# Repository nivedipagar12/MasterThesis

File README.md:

# MasterThesis
This repository contains the python code associated with my Master Thesis titled **"Evaluation and Feasibility Study of Analog Sensor Front-End using Impedance Spectroscopy for Biomedical Application"**. If you are new to this field, I suggest reading a little about the following topic:

- **Cole Model** : [Need of cole model and curve fitting for Body Composition Analysis](https://iopscience.iop.org/article/10.1088/0967-3334/34/10/1239)

1) **Folder Name: Curve Fitting**

This folder contains the main curve fitting algorithm. In the above mentioned cole modelling paper, you will find the formulas used to find the initial values of **x0, y0 and r0 (Equation 5)** and the simplified formula used to implement the **BFGS** algorithm to find the result as a function of **F(x0, y0, r0)** **(Equation 3)**. Upon finding the **center** **(x0,y0)** and **radius** **r0** of the imaginary circle, the **R0** and **Rinf** values can be calculated using distance formula as follows :

Point 1: x0,y0
Point 2: R0 or Rinf,0 .. Since the points R0 and Rinf are on x axis, their y-coordinate will be 0
distance = r0 .. We already know the distance between the two points (r0) 

Reverse engineering the distance formula, we can find R0 and Rinf as follows:
- R_{0} = x_{0} + \sqrt{r_{0}^{2} - y_{0}^{2}} .. to find R0
- R_{\infty}  = x_{0} - \sqrt{r_{0}^{2} - y_{0}^{2}} .. to find Rinf

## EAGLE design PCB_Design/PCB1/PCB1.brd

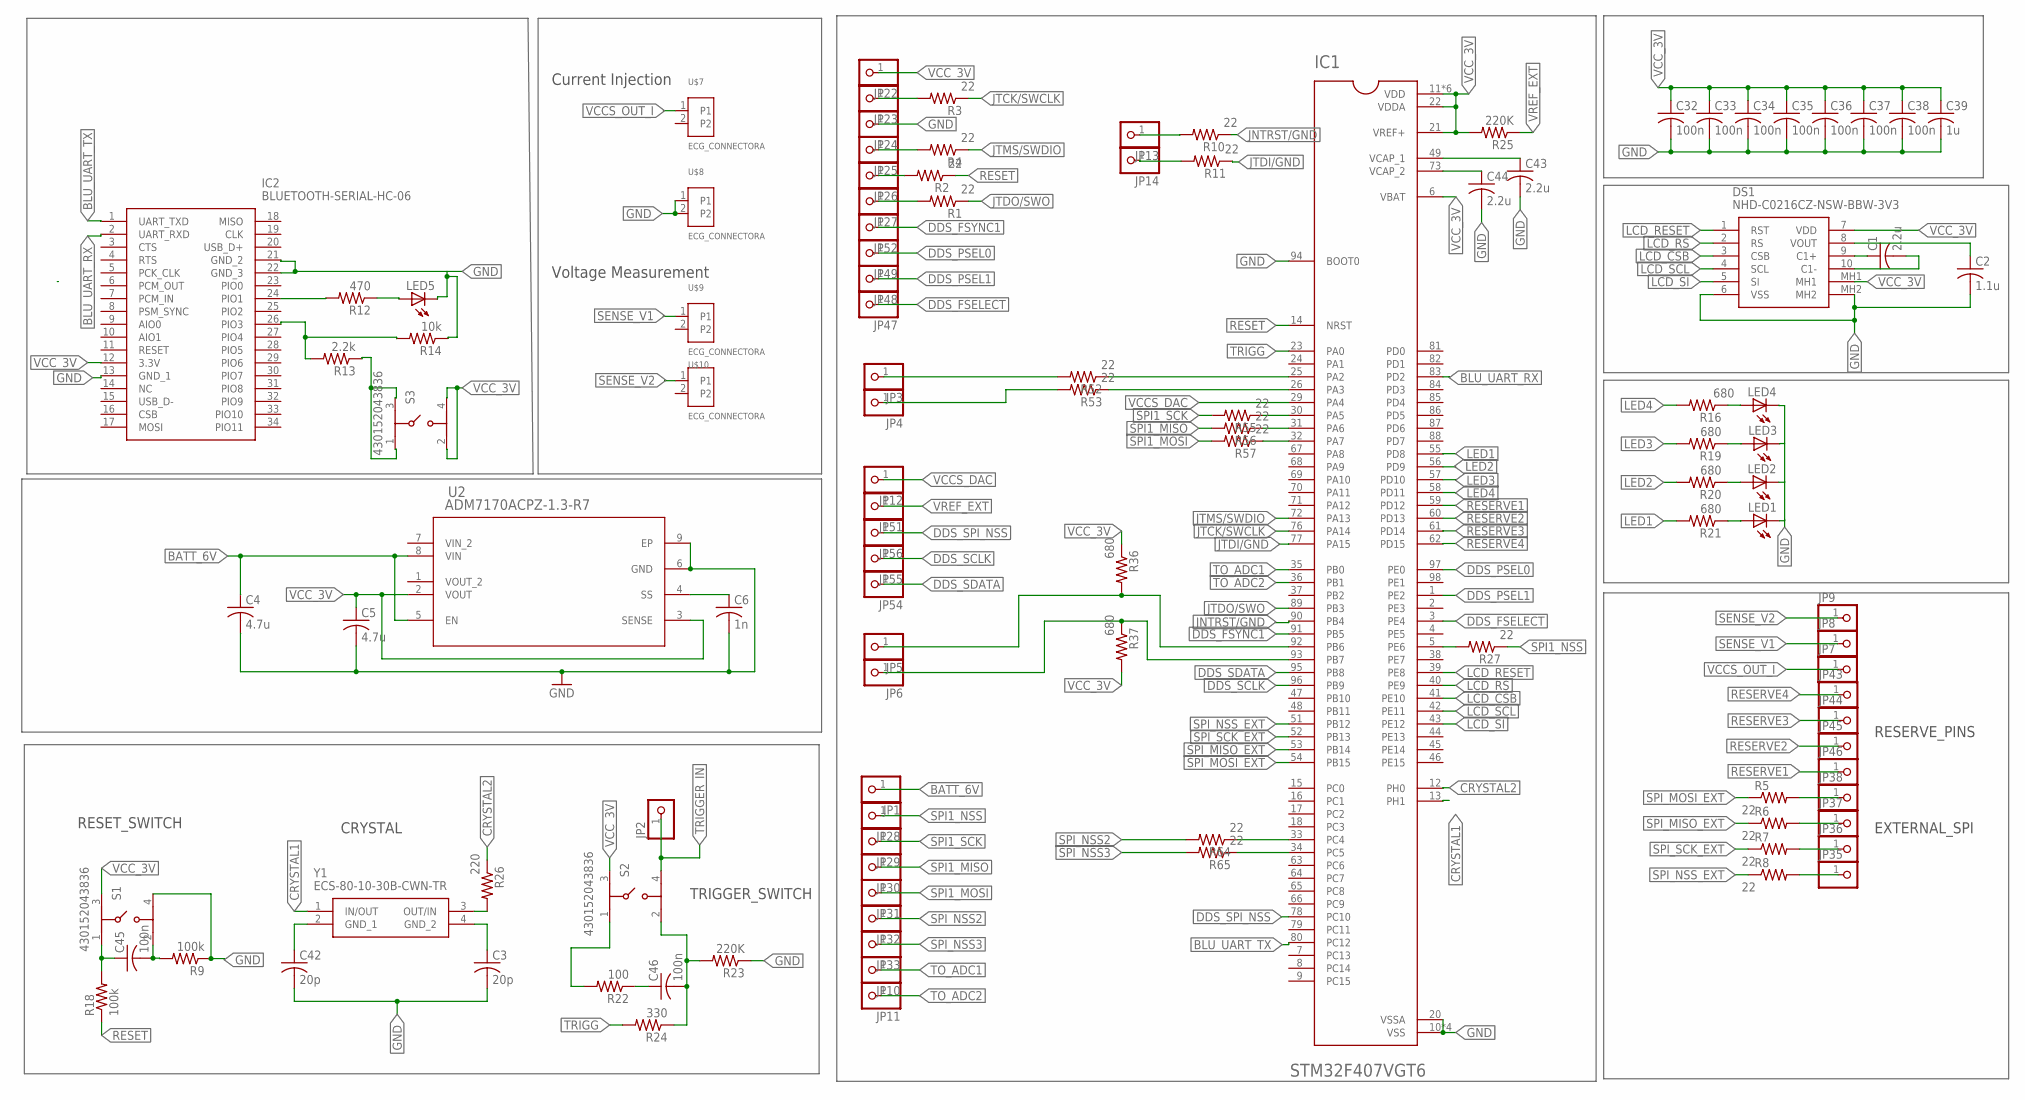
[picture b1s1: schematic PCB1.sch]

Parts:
C1, C43, C44: 2.2u; C0603
C2: 1.1u; C0603
C3, C42: 20p; C0603
C4, C5: 4.7u; C0603
C6: 1n; C0603
C32, C33, C34, C35, C36, C37, C38, C45, C46: 100n; C0603
C39: 1u; C0603
DS1: NHD-C0216CZ-NSW-BBW-3V3; NHDC0216CZNSWBBW3V3
IC1: STM32F407VGT6; QFP50P1600X1600X160-100N
IC2: BLUETOOTH-SERIAL-HC-06; BLUETOOTHSERIALHC06
JP1, JP2, JP3, JP4, JP5, JP6, JP7, JP8, JP9, JP10, JP11, JP12, JP13, JP14, JP22, JP23, JP24, JP25, JP26, JP27, JP28, JP29, JP30, JP31, JP32, JP33, JP35, JP36, JP37, JP38, JP43, JP44, JP45, JP46, JP47, JP48, JP49, JP51, JP52, JP54, JP55, JP56: PINHD-1X1; 1X01
LED1, LED2, LED3, LED4, LED5: LEDCHIPLED_1206; CHIPLED_1206
R1, R2, R3, R4, R5, R6, R7, R8, R10, R11, R27, R52, R53, R55, R56, R57, R64, R65: 22; R0603
R9, R18: 100k; R0603
R12: 470; R0603
R13: 2.2k; R0603
R14: 10k; R0603
R16, R19, R20, R21, R36, R37: 680; R0603
R22: 100; R0603
R23, R25: 220K; R0603
R24: 330; R0603
R26: 220; R0603
S1, S2, S3: 430152043836
U2: ADM7170ACPZ-1.3-R7; CP_8_21
U$7, U$8, U$9, U$10: ECG_CONNECTORA; ECG_CONNECTOR
Y1: ECS-80-10-30B-CWN-TR; ECS801830BAGNTR

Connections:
BATT_6V: C4.1, JP1.1, U2.5 (EN), U2.8 (VIN)
BLU_UART_RX: IC1.83 (PD2), IC2.2 (UART_RXD)
BLU_UART_TX: IC1.80 (PC12), IC2.1 (UART_TXD)
CRYSTAL1: IC1.13 (PH1), Y1.1 (IN/OUT)
CRYSTAL2: IC1.12 (PH0), R26.1
DDS_FSELECT: IC1.3 (PE4), JP47.1
DDS_FSYNC1: IC1.91 (PB5), JP52.1
DDS_PSEL0: IC1.97 (PE0), JP49.1
DDS_PSEL1: IC1.1 (PE2), JP48.1
DDS_SCLK: IC1.96 (PB9), JP55.1
DDS_SDATA: IC1.95 (PB8), JP54.1
DDS_SPI_NSS: IC1.78 (PC10), JP56.1
GND: C2.2, C3.2, C4.2, C5.2, C6.2, C32.2, C33.2, C34.2, C35.2, C36.2, C37.2, C38.2, C39.2, C42.1, C42.2, C43.2, C44.2, DS1.6 (VSS), DS1.MH2, IC1.10 (VSS), IC1.20 (VSSA), IC1.27 (VSS), IC1.74 (VSS), IC1.94 (BOOT0), IC1.99 (VSS), IC2.13 (GND_1), IC2.21 (GND_2), IC2.22 (GND_3), JP24.1, LED1.C, LED2.C, LED3.C, LED4.C, LED5.C, R9.1, R14.1, R23.1, S1.4, U2.6 (GND), U2.9 (EP), U$8.1, U$8.2, Y1.2 (GND_1)
I2C_SCL: IC1.92 (PB6), JP5.1, R36.2
I2C_SDA: IC1.93 (PB7), JP6.1, R37.1
JNTRST/GND: IC1.90 (PB4), R10.1
JTCK/SWCLK: IC1.76 (PA14), R3.1
JTDI/GND: IC1.77 (PA15), R11.1
JTDO/SWO: IC1.89 (PB3), R1.1
JTMS/SWDIO: IC1.72 (PA13), R4.1
LCD_CSB: DS1.3 (CSB), IC1.41 (PE10)
LCD_RESET: DS1.1 (RST), IC1.39 (PE8)
LCD_RS: DS1.2 (RS), IC1.40 (PE9)
LCD_SCL: DS1.4 (SCL), IC1.42 (PE11)
LCD_SI: DS1.5 (SI), IC1.43 (PE12)
LED1: IC1.55 (PD8), R21.2
LED2: IC1.56 (PD9), R20.2
LED3: IC1.57 (PD10), R19.2
LED4: IC1.58 (PD11), R16.2
unnamed: JP27.1, R1.2
unnamed: C1.1, DS1.9 (C1+)
unnamed: C45.2, R9.2, S1.2
unnamed: C1.2, DS1.10 (C1-)
unnamed: JP26.1, R2.2
unnamed: JP25.1, R4.2
unnamed: JP13.1, R10.2
unnamed: JP23.1, R3.2
unnamed: C2.1, DS1.8 (VOUT)
unnamed: JP35.1, R8.2
unnamed: C6.1, U2.4 (SS)
unnamed: JP36.1, R7.2
unnamed: JP37.1, R6.2
unnamed: JP38.1, R5.2
unnamed: JP14.1, R11.2
unnamed: R13.1, S3.1, S3.3
unnamed: LED2.A, R20.1
unnamed: LED3.A, R19.1
unnamed: LED4.A, R16.1
unnamed: LED1.A, R21.1
unnamed: IC2.24 (PIO1), R12.2
unnamed: LED5.A, R12.1
unnamed: R22.2, S2.1
unnamed: IC1.5 (PE6), R27.2
unnamed: C46.1, R22.1
unnamed: C43.1, IC1.49 (VCAP_1)
unnamed: C44.1, IC1.73 (VCAP_2)
unnamed: C46.2, R23.2, R24.1, S2.2
unnamed: C45.1, R18.2, S1.1
unnamed: C3.1, Y1.4 (GND_2)
unnamed: R26.2, Y1.3 (OUT/IN)
unnamed: IC2.26 (PIO3), R13.2, R14.2
unnamed: JP3.1, R52.2
unnamed: JP4.1, R53.2
unnamed: IC1.25 (PA2), R52.1
unnamed: IC1.26 (PA3), R53.1
unnamed: IC1.33 (PC4), R64.1
unnamed: IC1.30 (PA5), R55.1
unnamed: IC1.31 (PA6), R56.1
unnamed: IC1.32 (PA7), R57.1
unnamed: IC1.34 (PC5), R65.1
RESERVE1: IC1.59 (PD12), JP46.1
RESERVE2: IC1.60 (PD13), JP45.1
RESERVE3: IC1.61 (PD14), JP44.1
RESERVE4: IC1.62 (PD15), JP43.1
RESET: IC1.14 (NRST), R2.1, R18.1
SENSE_V1: JP8.1, U$9.1
SENSE_V2: JP9.1, U$10.1
SPI1_MISO: JP30.1, R56.2
SPI1_MOSI: JP31.1, R57.2
SPI1_NSS: JP28.1, R27.1
SPI1_SCK: JP29.1, R55.2
SPI_MISO_EXT: IC1.53 (PB14), R6.1
SPI_MOSI_EXT: IC1.54 (PB15), R5.1
SPI_NSS2: JP32.1, R64.2
SPI_NSS3: JP33.1, R65.2
SPI_NSS_EXT: IC1.51 (PB12), R8.1
SPI_SCK_EXT: IC1.52 (PB13), R7.1
TO_ADC1: IC1.35 (PB0), JP10.1
TO_ADC2: IC1.36 (PB1), JP11.1
TRIGG: IC1.23 (PA0), R24.2
TRIGGER_IN: JP2.1, S2.4
VCCS_DAC: IC1.29 (PA4), JP12.1
VCCS_OUT_I: JP7.1, U$7.1
VCC_3V: C5.1, C32.1, C33.1, C34.1, C35.1, C36.1, C37.1, C38.1, C39.1, DS1.7 (VDD), DS1.MH1, IC1.6 (VBAT), IC1.11 (VDD), IC1.19 (VDD), IC1.21 (VREF+), IC1.22 (VDDA), IC1.28 (VDD), IC1.50 (VDD), IC1.75 (VDD), IC1.100 (VDD), IC2.12 (3.3V), JP22.1, R25.2, R36.1, R37.2, S1.3, S2.3, S3.2, S3.4, U2.2 (VOUT), U2.3 (SENSE)
VREF_EXT: JP51.1, R25.1

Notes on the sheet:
Current Injection
Voltage Measurement
RESET_SWITCH
CRYSTAL
TRIGGER_SWITCH
RESERVE_PINS
EXTERNAL_SPI

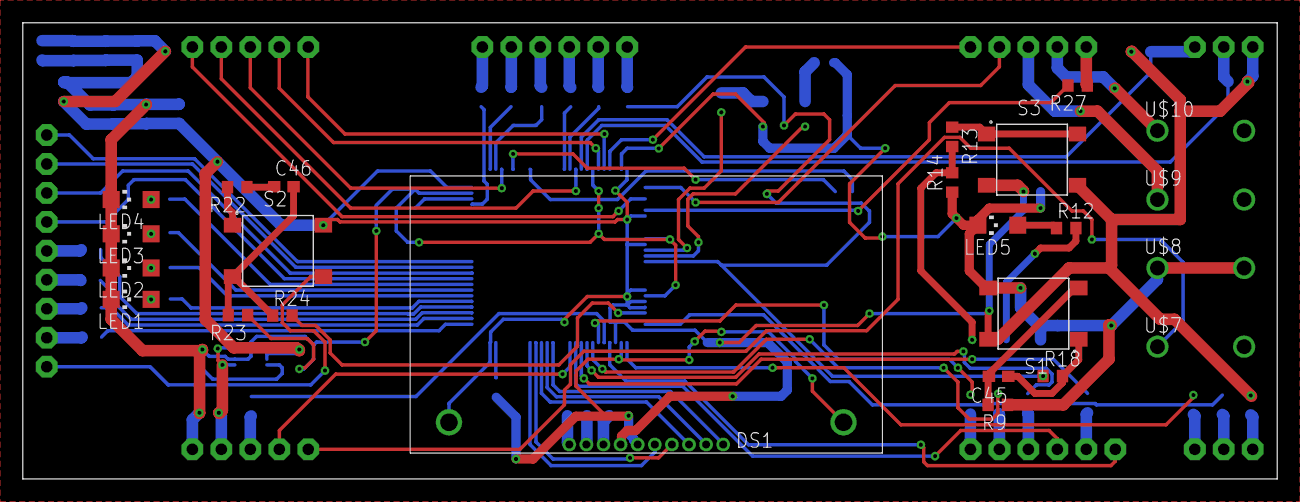
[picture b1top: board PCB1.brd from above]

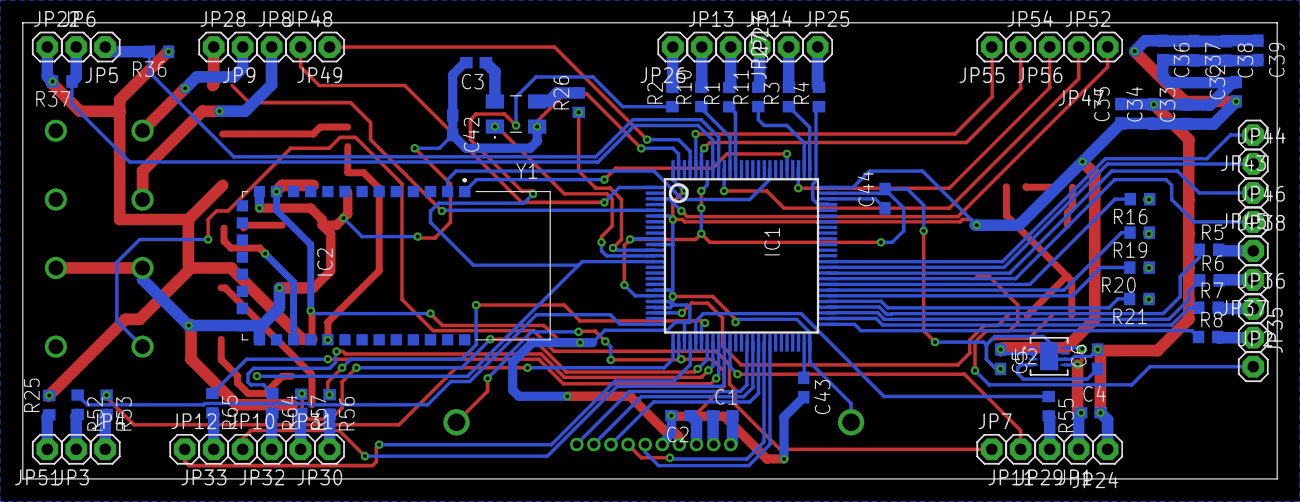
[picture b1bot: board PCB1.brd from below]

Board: 2 copper layers, 110.0 x 40.0 mm, 112 parts (88 on the bottom side), 95 nets.

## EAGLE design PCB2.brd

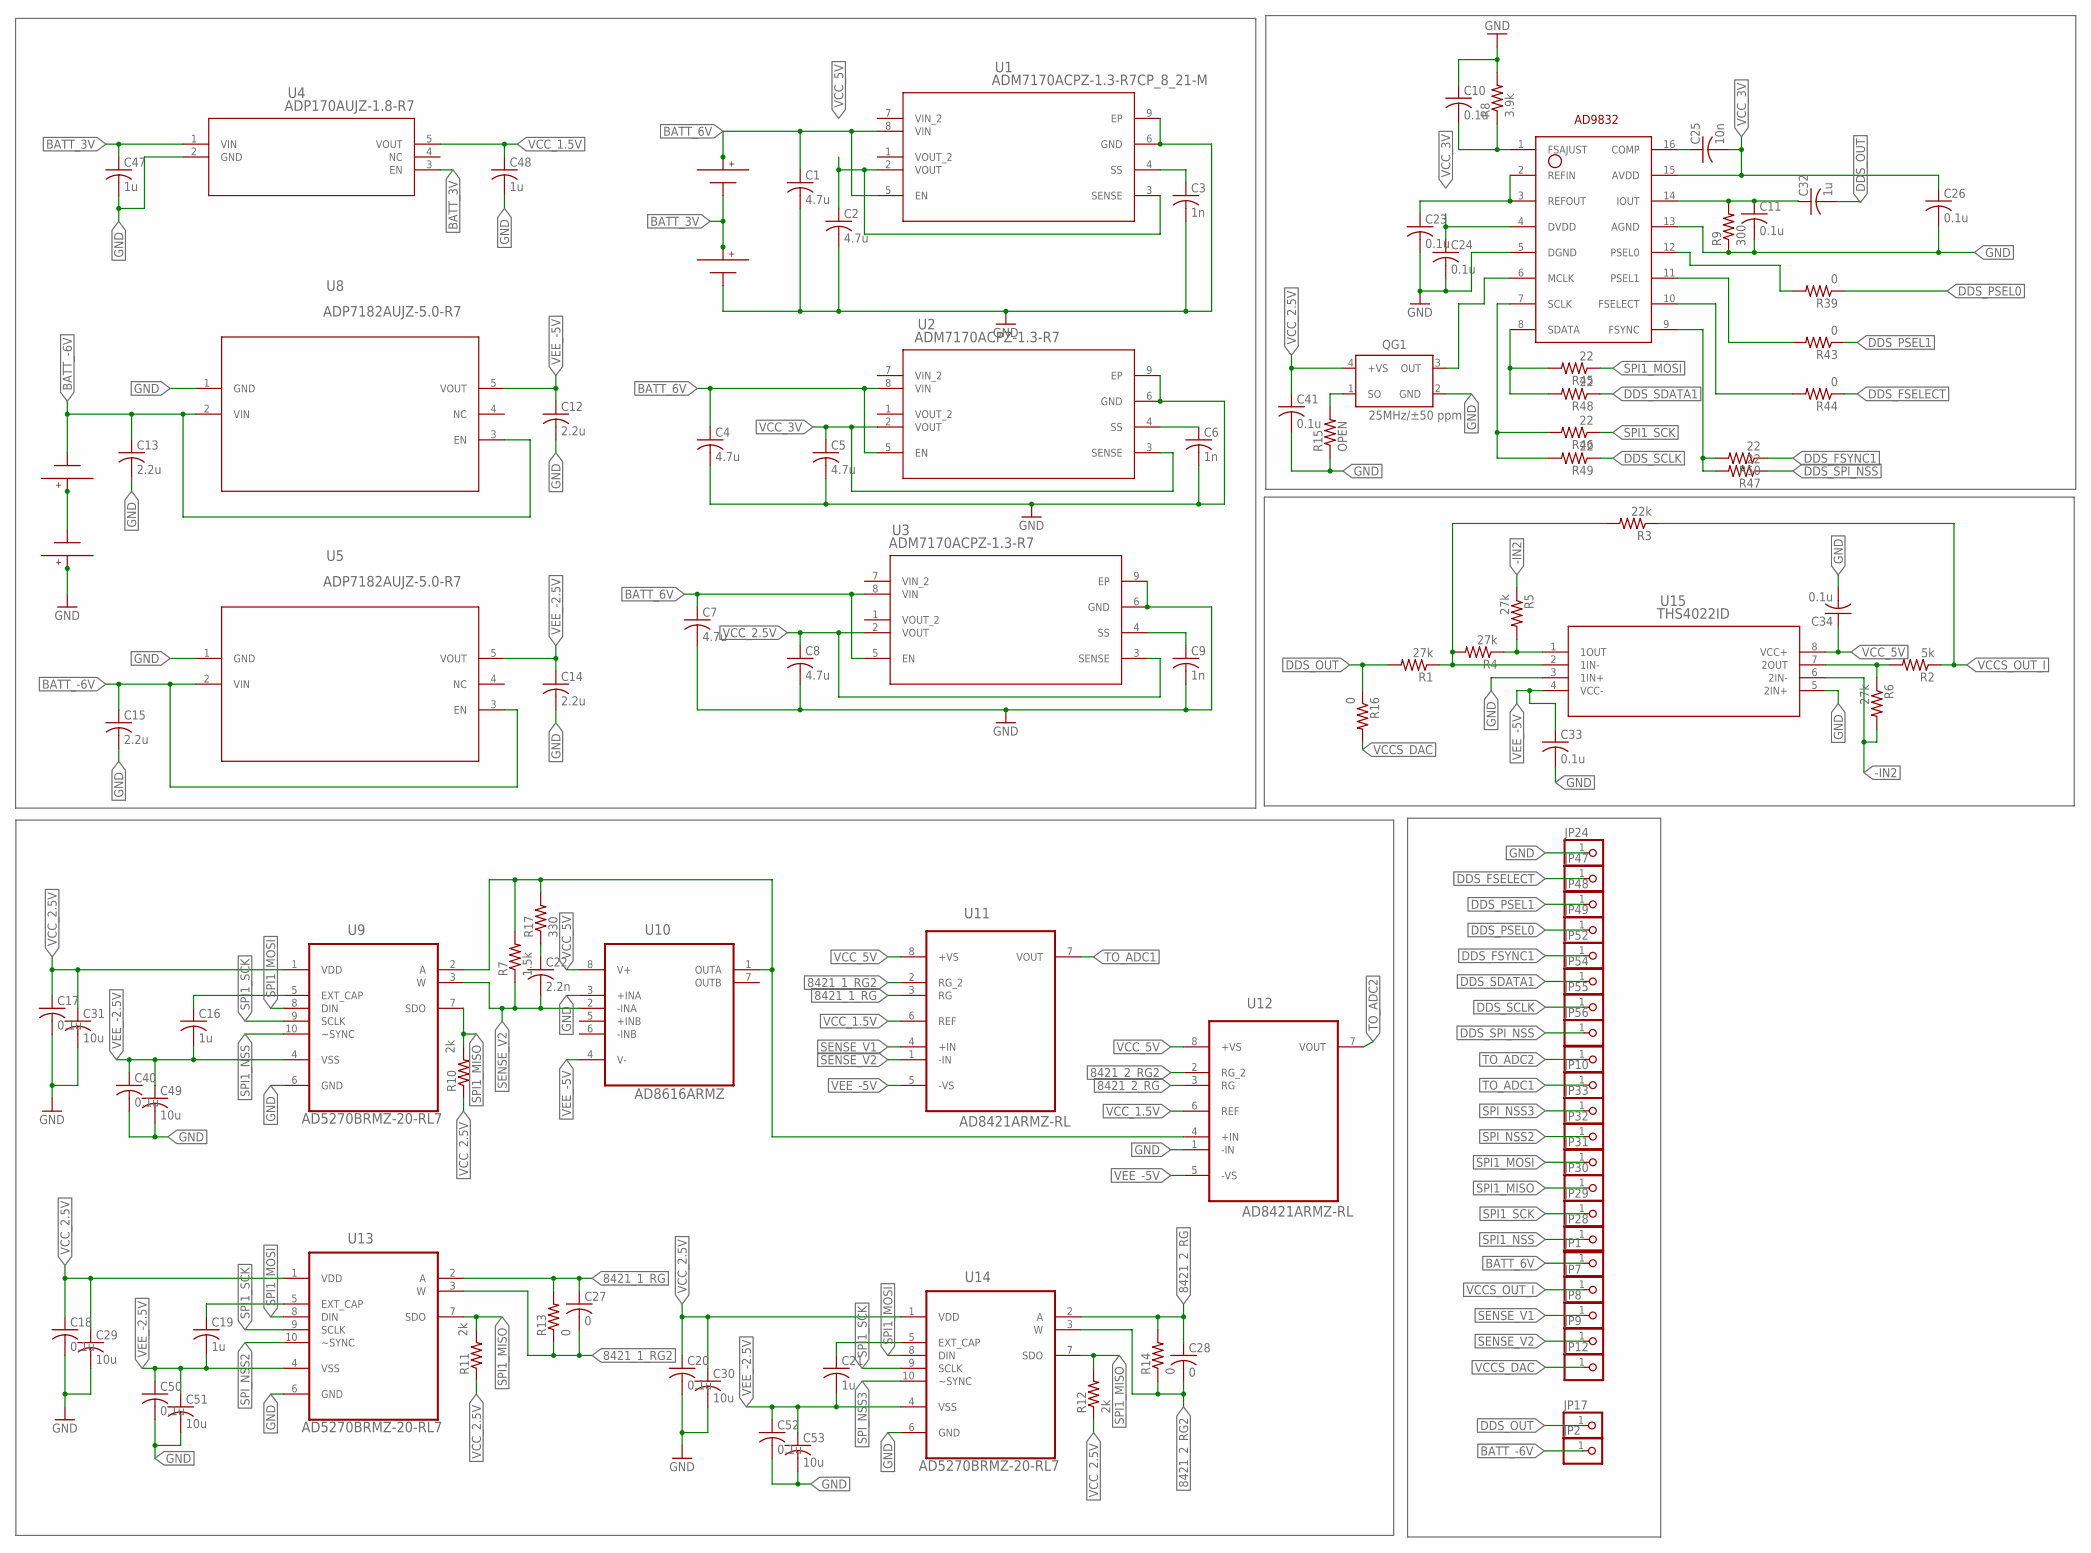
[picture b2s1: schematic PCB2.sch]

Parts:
C1, C2, C4, C5, C7, C8: 4.7u; C0603
C3, C6, C9: 1n; C0603
C10, C11, C17, C18, C20, C23, C24, C26, C33, C34, C40, C41, C50, C52: 0.1u; C0603
C12, C13, C14, C15: 2.2u; C0603
C16, C19, C21, C32, C47, C48: 1u; C0603
C22: 2.2n; C0603
C25: 10n; C0603
C27, C28: 0; C0603
C29, C30, C31, C49, C51, C53: 10u; C0603
JP1, JP2, JP7, JP8, JP9, JP10, JP11, JP12, JP17, JP24, JP28, JP29, JP30, JP31, JP32, JP33, JP47, JP48, JP49, JP52, JP54, JP55, JP56: PINHD-1X1; 1X01
QG1: 25MHz/±50 ppm; WE-SPXO_IQXO-542
R1, R4, R5, R6: 27k; R0603
R2: 5k; R0603
R3: 22k; R0603
R7: 1.5k; R0603
R8: 3.9k; R0603
R9: 300; R0603
R10, R11, R12: 2k; R0603
R13, R14, R16, R39, R43, R44: 0; R0603
R15: OPEN; R0603
R17: 330; R0603
R45, R46, R47, R48, R49, R50: 22; R0603
U1: ADM7170ACPZ-1.3-R7CP_8_21-M; CP_8_21-M
U2, U3: ADM7170ACPZ-1.3-R7; CP_8_21
U4: ADP170AUJZ-1.8-R7; UJ_5
U5, U8: ADP7182AUJZ-5.0-R7; UJ_5
U9, U13, U14: AD5270BRMZ-20-RL7; SOP50P490X110-10N
U10: AD8616ARMZ; SOP65P490X110-8N
U11, U12: AD8421ARMZ-RL; SOP65P490X110-8N
U15: THS4022ID; D8
U$1: AD9832; TSSOP16
U$2, U$3, U$4, U$5: BAT-HLD-001

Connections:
8421_1_RG: C27.1, R13.2, U11.3 (RG), U13.2 (A)
8421_1_RG2: C27.2, R13.1, U11.2 (RG_2), U13.3 (W)
8421_2_RG: C28.1, R14.2, U12.3 (RG), U14.2 (A)
8421_2_RG2: C28.2, R14.1, U12.2 (RG_2), U14.3 (W)
-IN2: R5.1, R6.2, U15.6 (2IN-)
BATT_3V: C47.1, U4.1 (VIN), U4.3 (EN), U$2.-, U$3.+@1 (+), U$3.+@2 (+)
BATT_6V: C1.1, C4.1, C7.1, JP1.1, U1.5 (EN), U1.8 (VIN), U2.5 (EN), U2.8 (VIN), U3.5 (EN), U3.8 (VIN), U$2.+@1 (+), U$2.+@2 (+)
BATT_-6V: C13.1, C15.1, JP2.1, U5.2 (VIN), U5.3 (EN), U8.2 (VIN), U8.3 (EN), U$4.-
DDS_FSELECT: JP47.1, R44.1
DDS_FSYNC1: JP52.1, R50.1
DDS_OUT: C32.2, JP17.1, R1.2, R16.1
DDS_PSEL0: JP49.1, R39.1
DDS_PSEL1: JP48.1, R43.1
DDS_SCLK: JP55.1, R49.1
DDS_SDATA1: JP54.1, R48.1
DDS_SPI_NSS: JP56.1, R47.1
GND: C1.2, C2.2, C3.2, C4.2, C5.2, C6.2, C7.2, C8.2, C9.2, C10.1, C11.2, C12.2, C13.2, C14.2, C15.2, C17.2, C18.2, C20.2, C23.2, C24.2, C26.2, C29.2, C30.2, C31.2, C33.2, C34.2, C40.2, C41.2, C47.2, C48.2, C49.2, C50.2, C51.2, C52.2, C53.2, JP24.1, QG1.2 (GND), R8.2, R9.1, R15.1, U1.6 (GND), U1.9 (EP), U2.6 (GND), U2.9 (EP), U3.6 (GND), U3.9 (EP), U4.2 (GND), U5.1 (GND), U8.1 (GND), U9.6 (GND), U10.3 (+INA), U12.1 (-IN), U13.6 (GND), U14.6 (GND), U15.3 (1IN+), U15.5 (2IN+), U$1.5 (DGND), U$1.13 (AGND), U$3.-, U$5.+@1 (+), U$5.+@2 (+)
unnamed: C11.1, C32.1, R9.2, U$1.14 (IOUT)
unnamed: C6.1, U2.4 (SS)
unnamed: R47.2, R50.2, U$1.9 (FSYNC)
unnamed: C3.1, U1.4 (SS)
unnamed: C22.1, R17.1
unnamed: C16.1, U9.5 (EXT_CAP)
unnamed: R7.2, R17.2, U9.2 (A), U10.1 (OUTA), U12.4 (+IN)
unnamed: C9.1, U3.4 (SS)
unnamed: U$4.+@1 (+), U$4.+@2 (+), U$5.-
unnamed: R45.2, R48.2, U$1.8 (SDATA)
unnamed: C19.1, U13.5 (EXT_CAP)
unnamed: C10.2, R8.1, U$1.1 (FSAJUST)
unnamed: C25.1, U$1.16 (COMP)
unnamed: C21.1, U14.5 (EXT_CAP)
unnamed: C23.1, U$1.2 (REFIN), U$1.3 (REFOUT)
unnamed: QG1.1 (SO), R15.2
unnamed: R46.2, R49.2, U$1.7 (SCLK)
unnamed: R2.2, R6.1, U15.7 (2OUT)
unnamed: QG1.3 (OUT), U$1.6 (MCLK)
unnamed: R4.1, R5.2, U15.1 (1OUT)
unnamed: R1.1, R3.2, R4.2, U15.2 (1IN-)
unnamed: R44.2, U$1.10 (FSELECT)
unnamed: R43.2, U$1.11 (PSEL1)
unnamed: R39.2, U$1.12 (PSEL0)
SENSE_V1: JP8.1, U11.4 (+IN)
SENSE_V2: C22.2, JP9.1, R7.1, U9.3 (W), U10.2 (-INA), U11.1 (-IN)
SPI1_MISO: JP30.1, R10.2, R11.2, R12.2, U9.7 (SDO), U13.7 (SDO), U14.7 (SDO)
SPI1_MOSI: JP31.1, R45.1, U9.8 (DIN), U13.8 (DIN), U14.8 (DIN)
SPI1_NSS: JP28.1, U9.10 (~SYNC)
SPI1_SCK: JP29.1, R46.1, U9.9 (SCLK), U13.9 (SCLK), U14.9 (SCLK)
SPI_NSS2: JP32.1, U13.10 (~SYNC)
SPI_NSS3: JP33.1, U14.10 (~SYNC)
TO_ADC1: JP10.1, U11.7 (VOUT)
TO_ADC2: JP11.1, U12.7 (VOUT)
VCCS_DAC: JP12.1, R16.2
VCCS_OUT_I: JP7.1, R2.1, R3.1
VCC_1.5V: C48.1, U4.5 (VOUT), U11.6 (REF), U12.6 (REF)
VCC_2.5V: C8.1, C17.1, C18.1, C20.1, C29.1, C30.1, C31.1, C41.1, QG1.4 (+VS), R10.1, R11.1, R12.1, U3.2 (VOUT), U3.3 (SENSE), U9.1 (VDD), U13.1 (VDD), U14.1 (VDD)
VCC_3V: C5.1, C24.1, C25.2, C26.1, U2.2 (VOUT), U2.3 (SENSE), U$1.4 (DVDD), U$1.15 (AVDD)
VCC_5V: C2.1, C34.1, U1.2 (VOUT), U1.3 (SENSE), U10.8 (V+), U11.8 (+VS), U12.8 (+VS), U15.8 (VCC+)
VEE_-2.5V: C14.1, C16.2, C19.2, C21.2, C40.1, C49.1, C50.1, C51.1, C52.1, C53.1, U5.5 (VOUT), U9.4 (VSS), U13.4 (VSS), U14.4 (VSS)
VEE_-5V: C12.1, C33.1, U8.5 (VOUT), U10.4 (V-), U11.5 (-VS), U12.5 (-VS), U15.4 (VCC-)

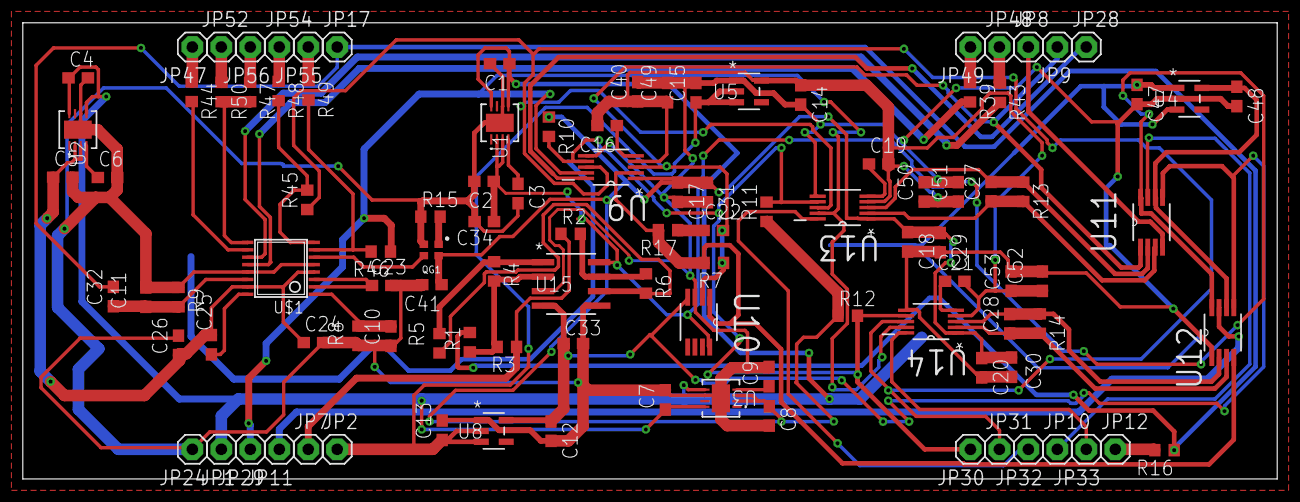
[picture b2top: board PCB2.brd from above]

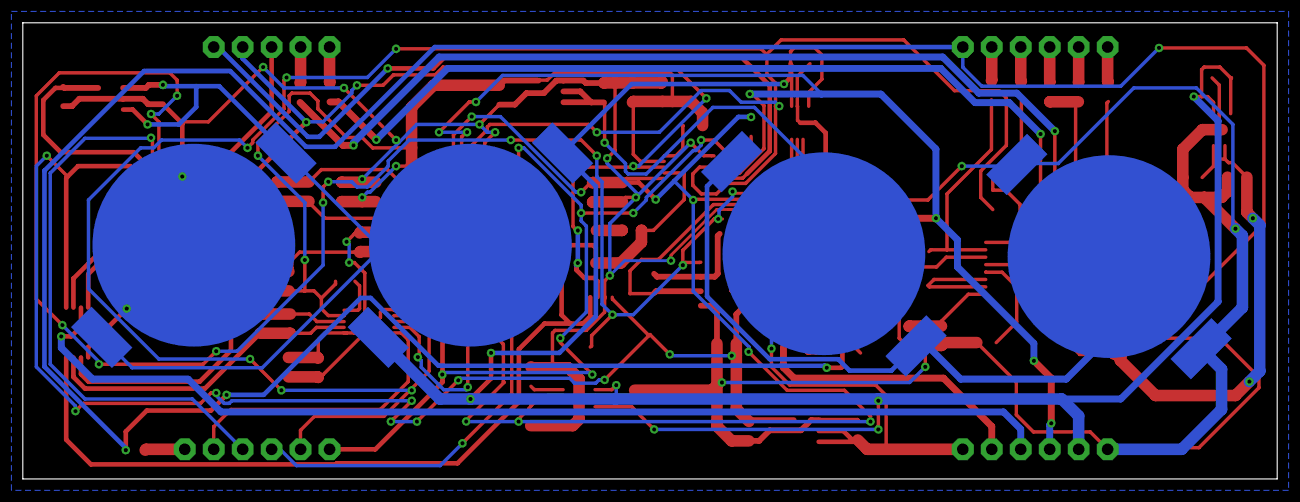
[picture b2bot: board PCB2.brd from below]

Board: 2 copper layers, 110.0 x 40.0 mm, 111 parts (4 on the bottom side), 59 nets.

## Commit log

2019-03-13 Created main.py
    This file contains a curve fitting based nonlinear multiple unknown variable iterative algorithm
2019-03-13 Added sample workbook
    This file contains sample excel workbook required to run the code. The excel file needs to be in the same folder as the main.py file.
2019-03-13 edited comments
    Edited the comment on file association
2019-03-13 added description of curve fitting folder
    Added theoretical background about cole modelling and details of the formulas used in the curve fitting code
2019-03-13 changed the structure of the description
2019-03-13 changes to the structure
    some minor changes to the structure of the description
2019-03-13 minor changes
2019-07-15 Uploaded schematic and board files
    Uploaded Eagle files (schematic and board) for Master Thesis PCB
2019-07-15 Info about PCB
    Added information about Eagle files
2019-07-15 Uploaded image files
    Uploaded PCB overview and system overview image files
2019-07-15 Create abc
2019-07-15 Create cvb
2019-07-15 PCB relevant files
    Uploaded all Eagle and image files related to PCB1
2019-07-15 Create acv
2019-07-15 PCB2 relevant files
    Uploaded all files related to PCB2
2019-07-15 overview files
    Uploaded image files showing overview of System design and PCB design

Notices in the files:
parts and their libraries:
Crystal25MHz: Copyright: Würth Elektronik
